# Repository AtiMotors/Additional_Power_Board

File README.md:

# Additional_Power_Board
 Additional Power board design for Vecow/Rudy integration for V3.0

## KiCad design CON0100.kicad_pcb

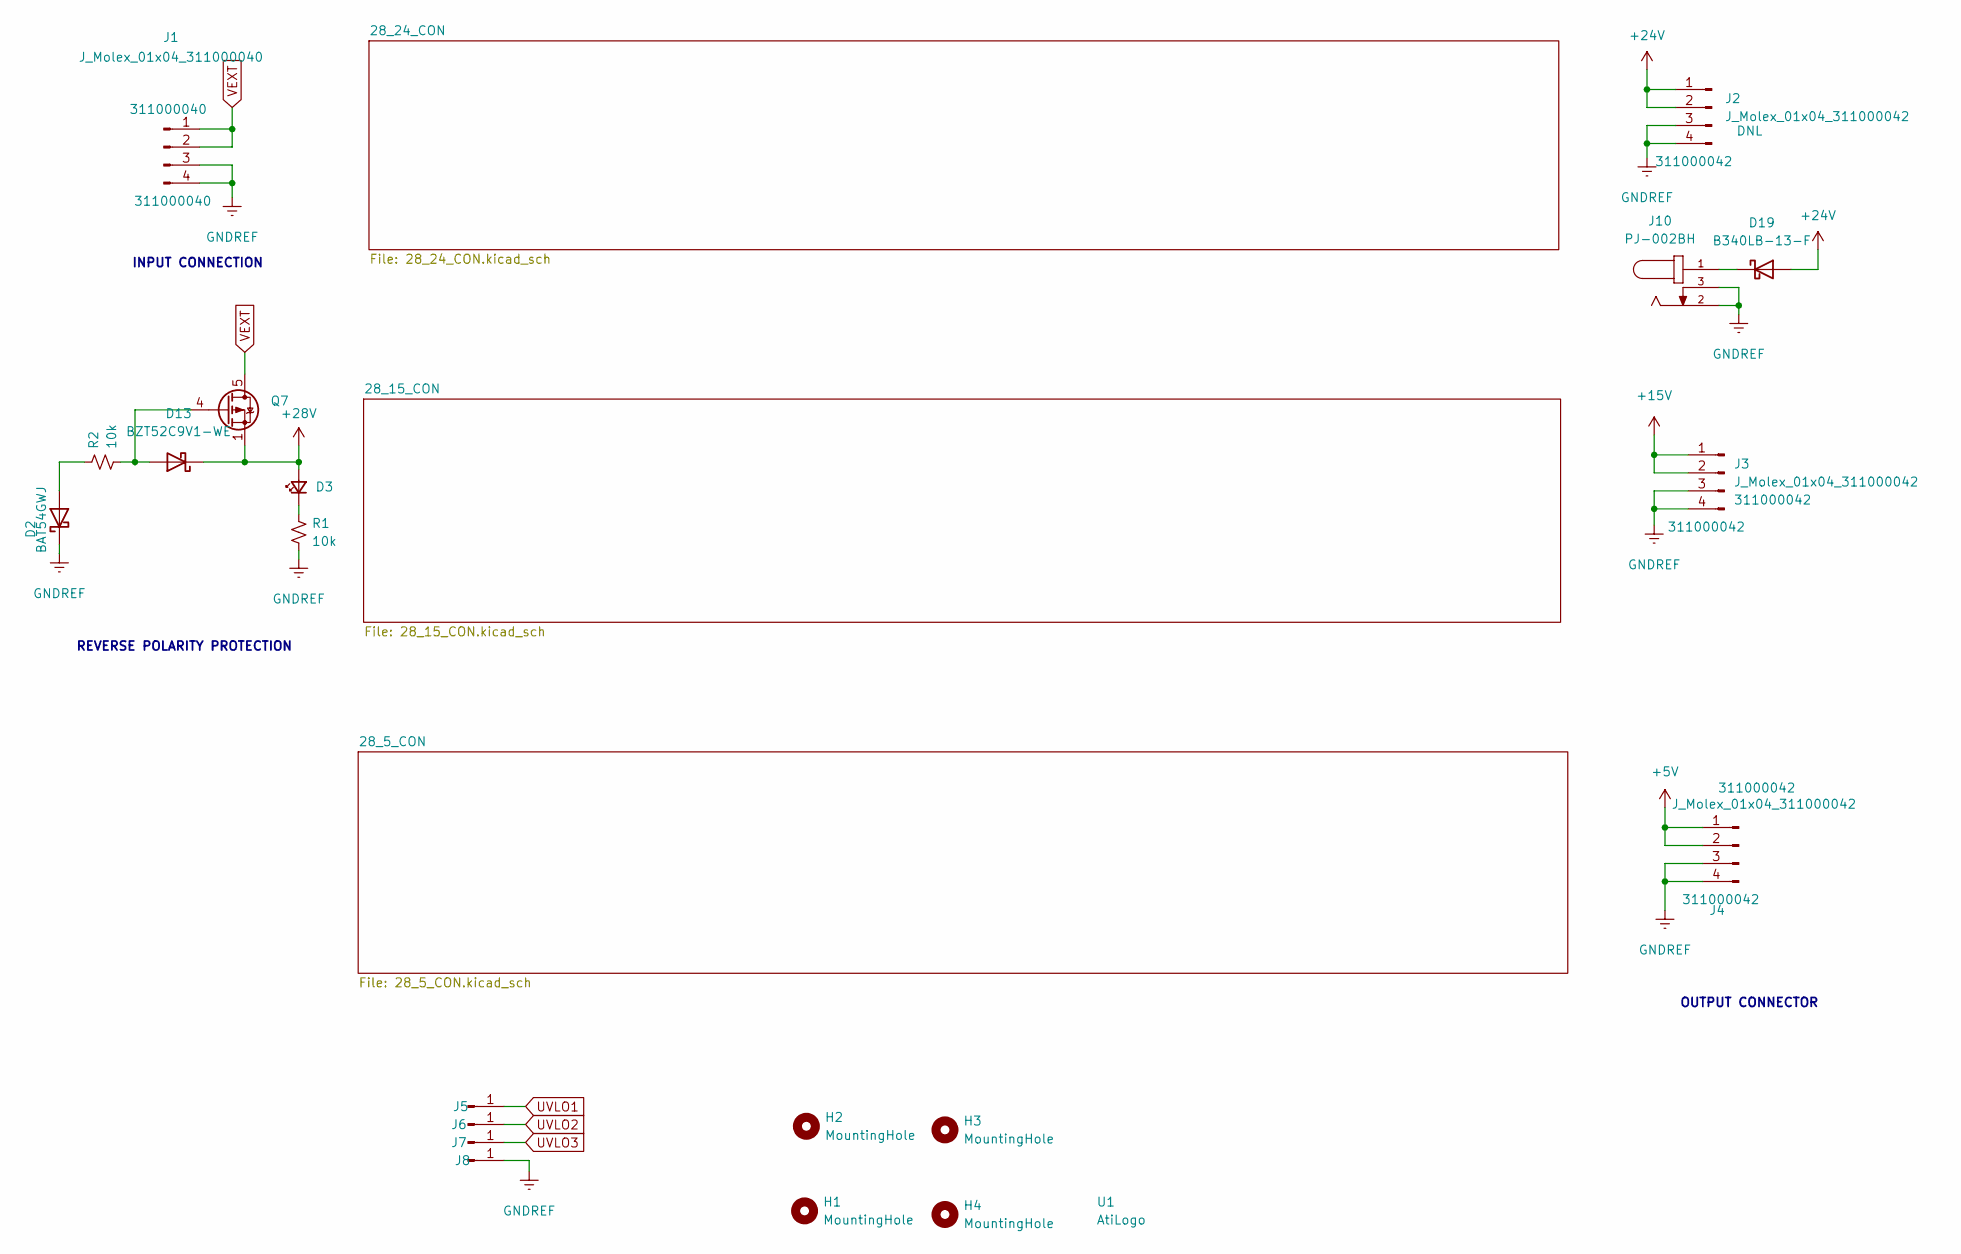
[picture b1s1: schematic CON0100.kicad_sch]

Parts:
D2: MPN BAT54GWJ
D3: D_LED_0603_Green_150060GS75000; LED_0603_1608Metric_Pad1.05x0.95mm_HandSolder; MPN 150060GS75000
D13: MPN BZT52C9V1-WE
D19: B340LB-13-F; D_SMB
H1, H2, H3, H4: MountingHole; MountingHole_3.5mm
J1: J_Molex_01x04_311000040; Molex_311000040_4pos_1row_2.54mm_PolA; MPN 311000040
J2, J3, J4: J_Molex_01x04_311000042; Molex_311000042_4pos_1row_2.54mm_PolC; MPN 311000042
J5, J6, J7, J8: Conn_01x01_Male; PinHeader_1x01_P2.54mm_Vertical
J10: PJ-002BH; CUI_PJ-002BH; MPN Manufacturer recommendations
Q7: MPN SQJ479EP-T1_GE3
R1: MPN ERJ-3EKF1002V
R2: R_10k_0603_ERJ-3EKF1002V; MPN ERJ-3EKF1002V
U1: AtiLogo; atilogo_19.06_10.16mm

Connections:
+5V: J4.1, J4.2; also elsewhere on the board
+15V: J3.1, J3.2; also elsewhere on the board
+24V: D19.2 (A), J2.1, J2.2; also elsewhere on the board
+28V: D3.2 (A), D13.1 (K), Q7.1 (S), Q7.2 (S), Q7.3 (S); also elsewhere on the board
GNDREF: D2.1 (K), J1.3, J1.4, J2.3, J2.4, J3.3, J3.4, J4.3, J4.4, J8.1, J10.2, J10.3, R1.2; also elsewhere on the board
unnamed: D2.2 (A), R2.1
unnamed: D3.1 (K), R1.1
unnamed: D19.1 (K), J10.1
unnamed: D13.2 (A), Q7.4 (G), R2.2
UVLO1: J5.1; also elsewhere on the board
UVLO2: J6.1; also elsewhere on the board
UVLO3: J7.1; also elsewhere on the board
VEXT: J1.1, J1.2, Q7.5 (D)

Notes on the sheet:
INPUT CONNECTION
REVERSE POLARITY PROTECTION
OUTPUT CONNECTOR

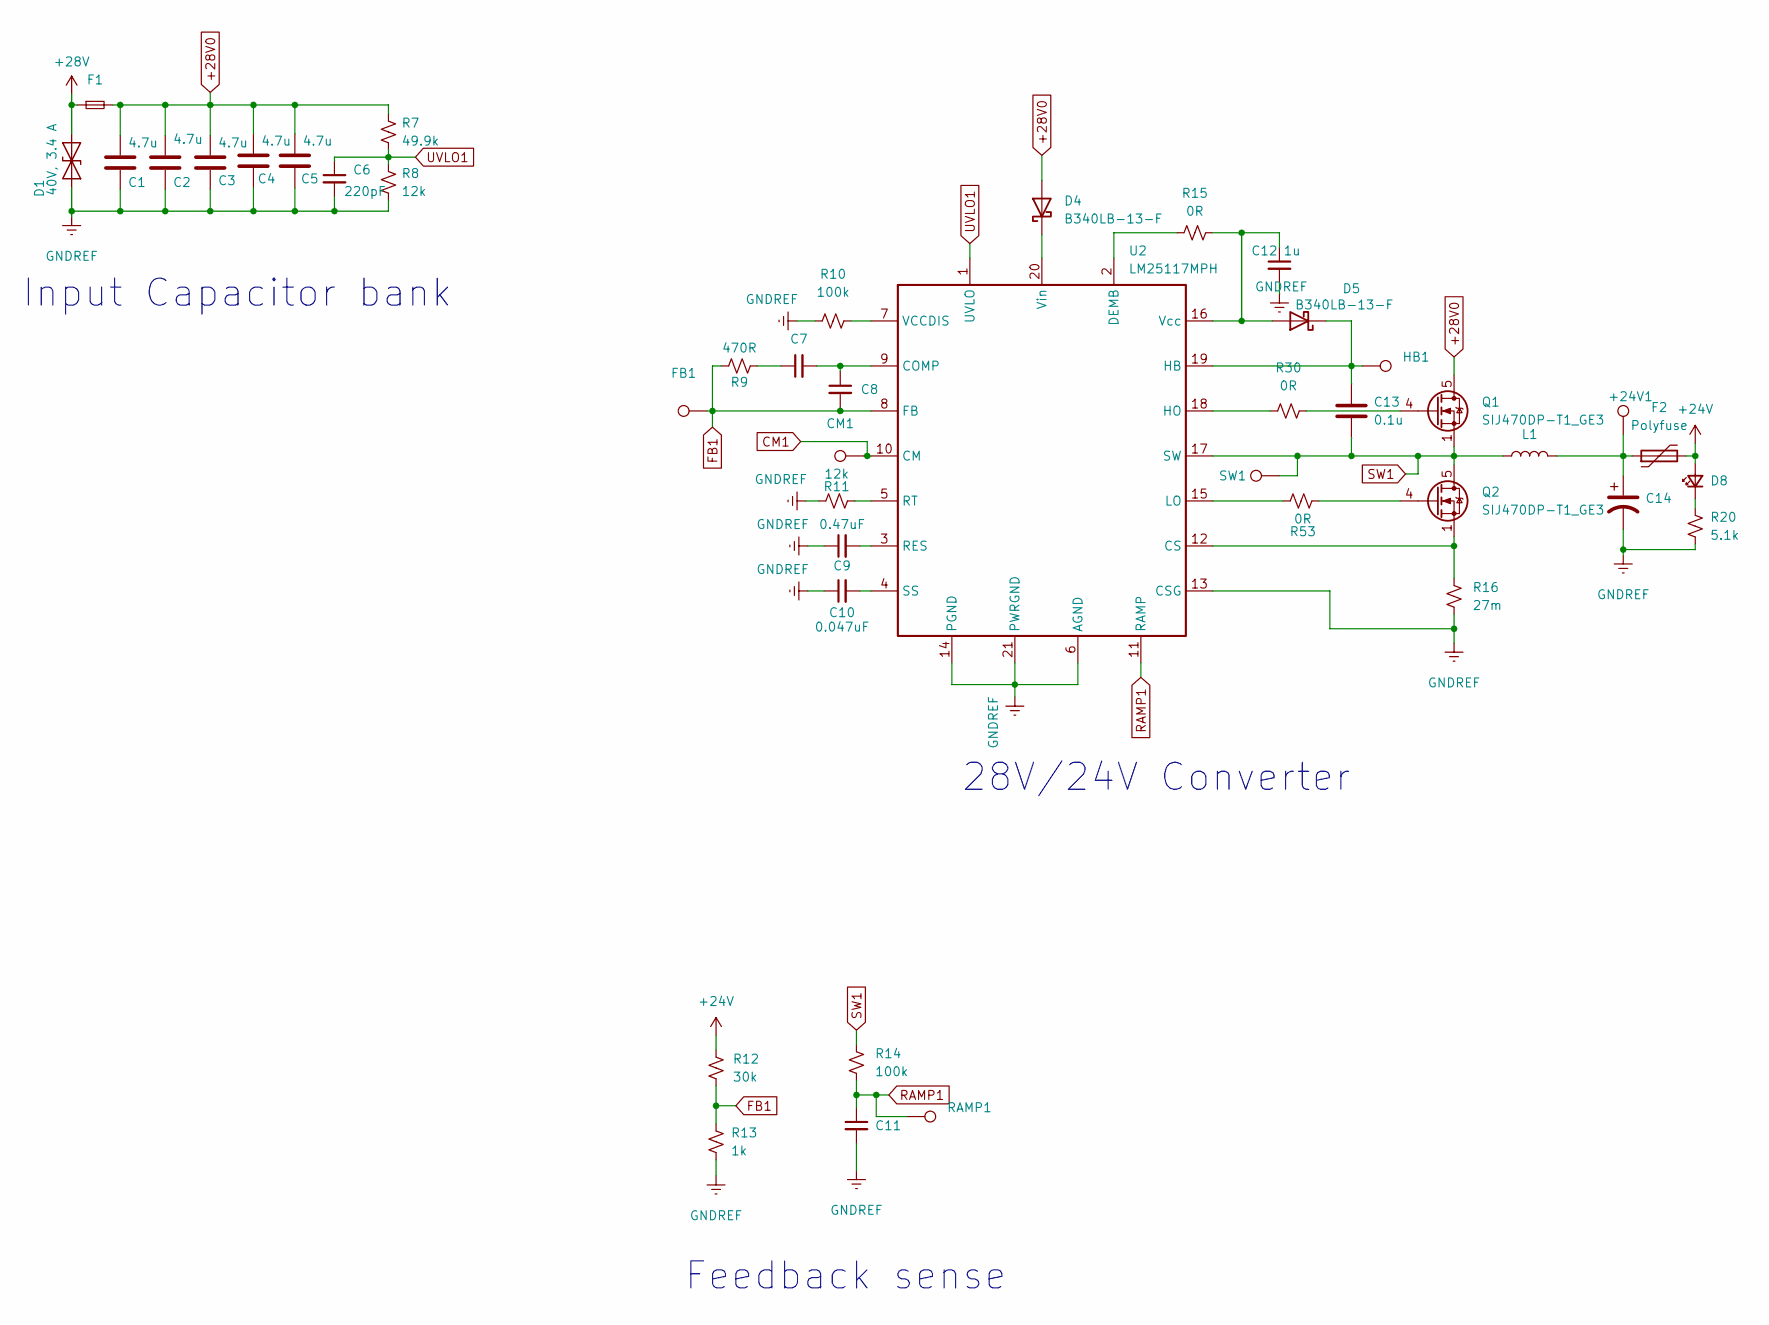
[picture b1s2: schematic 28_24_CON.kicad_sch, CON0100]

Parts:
+24V1: (no value)
C1, C2, C3, C4, C5: C_4.7u_1206_CL31B475KAHNNNE; C_1206_3216Metric_Pad1.33x1.80mm_HandSolder; MPN CL31B475KAHNNNE
C6: C_0603_220pF_50V_ECJ-1VC1H221J; C_0603_1608Metric_Pad1.08x0.95mm_HandSolder; MPN ECJ-1VC1H221J
C7: C_0.01uf_0603_50V_ECJ-1VB1H103K; C_0603_1608Metric_Pad1.08x0.95mm_HandSolder; MPN ECJ-1VB1H103K
C8: C_10pF_0603_GCM1885C1H100JA16D; C_0603_1608Metric_Pad1.08x0.95mm_HandSolder; MPN GCM1885C1H100JA16D
C9: C_0603_0.47uF_25V_CGA3E3X7R1E474K080AB; C_0603_1608Metric_Pad1.08x0.95mm_HandSolder; MPN CGA3E3X7R1E474K080AB
C10: C_0603_0.047uF_16V_10%_ECJ-1VB1C473K; C_0603_1608Metric_Pad1.08x0.95mm_HandSolder; MPN ECJ-1VB1C473K
C11: C_820pF_0603_50V_GCM1885C1H821JA16D; C_0603_1608Metric_Pad1.08x0.95mm_HandSolder; MPN GCM1885C1H821JA16D
C12: C_1uf_0603_GCJ188R71E105KA01D; C_0603_1608Metric_Pad1.08x0.95mm_HandSolder; MPN GCJ188R71E105KA01D
C13: C_0603_0.1u_50V_C0603C104K5RACAUTO; C_0603_1608Metric_Pad1.08x0.95mm_HandSolder; Voltage 50V; MPN C0603C104K5RACAUTO
C14: C_0.22uF_RAD_50V_20%; C_Elec_4x5.4; MPN UWP1HR22MCL1GB
CM1: (no value)
D1: D_TVS_40V_ATV02W360B-HF; D_SOD-123F; MPN ATV02W360B-HF
D4, D5: B340LB-13-F; D_SMB
D8: D_LED_0603_Blue_150060BS75000; LED_0603_1608Metric_Pad1.05x0.95mm_HandSolder; MPN 150060BS75000
F1: Fuse_1206_SlowBlow_SF-1206SA350M-2; Fuse_0603_1608Metric_Pad1.05x0.95mm_HandSolder; MPN SF-1206SA350M-2
F2: Polyfuse; Fuse_2920_7451Metric_Pad2.10x5.45mm_HandSolder
FB1: (no value)
HB1: (no value)
L1: L_22uH_12A_37mOhms_SMD_12.5mmx13.5mm; L_Bourns_SRP1245A; MPN SRP1265A-220M
Q1, Q2: SIJ470DP-T1_GE3; PowerPAK_SO-8_Single; MPN SIJ470DP-T1_GE3
R7: R_49.9k_0603_ERJ3EKF4992V; R_0603_1608Metric_Pad0.98x0.95mm_HandSolder; MPN ERJ-3EKF4992V
R8, R11: R_12k_0603_ERJ3EKF1202V; R_0603_1608Metric_Pad0.98x0.95mm_HandSolder; MPN ERJ-3EKF1202V
R9: R_470R_0603_ERJ-3EKF4700V; R_0603_1608Metric_Pad0.98x0.95mm_HandSolder; MPN ERJ-3EKF4700V
R10: R_100k_0603_1/10W_CRGP0603F100K; R_0603_1608Metric_Pad0.98x0.95mm_HandSolder; MPN ERJ-3EKF1003V
R12: R_30k_0603_ERJ-PB3B3002V; R_0603_1608Metric_Pad0.98x0.95mm_HandSolder; MPN ERJ-PB6B3002V
R13: R_1k_0603_ERJ-3EKF1001V; R_0603_1608Metric_Pad0.98x0.95mm_HandSolder; MPN 3EKF1001V
R14: R_100k_0603_0.1%_ERA3APB104V; R_0603_1608Metric_Pad0.98x0.95mm_HandSolder; MPN ERA3APB104V
R15, R30, R53: R_0R_0603_ERJ-3GEY0R00V; R_0603_1608Metric_Pad0.98x0.95mm_HandSolder; MPN ERJ-3GEY0R00V
R16: R_27mOhms_0805_ERJ-6BWFR027V; R_0805_2012Metric_Pad1.20x1.40mm_HandSolder; MPN ERJ-6BWFR027V
R20: R_5.1k_0603_RC0603FR-075K1L; R_0603_1608Metric_Pad0.98x0.95mm_HandSolder; MPN RC0603FR-0715KL
RAMP1: (no value)
SW1: (no value)
U2: LM25117MPH; SOP65P640X110-21N; MPN LM25117MPH/NOPB

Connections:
+24V: D8.2 (A), F2.2, R12.1; also elsewhere on the board
+28V: D1.2 (A2), F1.1; also elsewhere on the board
+28V0: C1.1, C2.1, C3.1, C4.1, C5.1, D4.2 (A), F1.2, Q1.5 (D), R7.1
CM1: CM1.1, U2.10 (CM)
FB1: C8.2, FB1.1, R9.1, R12.2, R13.1, U2.8 (FB)
GNDREF: C1.2, C2.2, C3.2, C4.2, C5.2, C6.2, C9.1, C10.1, C11.2, C12.2, C14.2, D1.1 (A1), R8.2, R10.1, R11.1, R13.2, R16.2, R20.2, U2.6 (AGND), U2.13 (CSG), U2.14 (PGND), U2.21 (PWRGND); also elsewhere on the board
unnamed: C7.1, R9.2
unnamed: C7.2, C8.1, U2.9 (COMP)
unnamed: C9.2, U2.3 (RES)
unnamed: C10.2, U2.4 (SS)
unnamed: C12.1, D5.2 (A), R15.2, U2.16 (Vcc)
unnamed: C13.1, D5.1 (K), HB1.1, U2.19 (HB)
unnamed: +24V1.1, C14.1, F2.1, L1.2
unnamed: D4.1 (K), U2.20 (Vin)
unnamed: D8.1 (K), R20.1
unnamed: Q1.4 (G), R30.2
unnamed: Q2.1 (S), Q2.2 (S), Q2.3 (S), R16.1, U2.12 (CS)
unnamed: Q2.4 (G), R53.2
unnamed: R10.2, U2.7 (VCCDIS)
unnamed: R11.2, U2.5 (RT)
unnamed: R15.1, U2.2 (DEMB)
unnamed: R30.1, U2.18 (HO)
unnamed: R53.1, U2.15 (LO)
RAMP1: C11.1, R14.2, RAMP1.1, U2.11 (RAMP)
SW1: C13.2, L1.1, Q1.1 (S), Q1.2 (S), Q1.3 (S), Q2.5 (D), R14.1, SW1.1, U2.17 (SW)
UVLO1: C6.1, R7.2, R8.1, U2.1 (UVLO); also elsewhere on the board

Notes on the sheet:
Feedback sense
28V/24V Converter
Input Capacitor bank

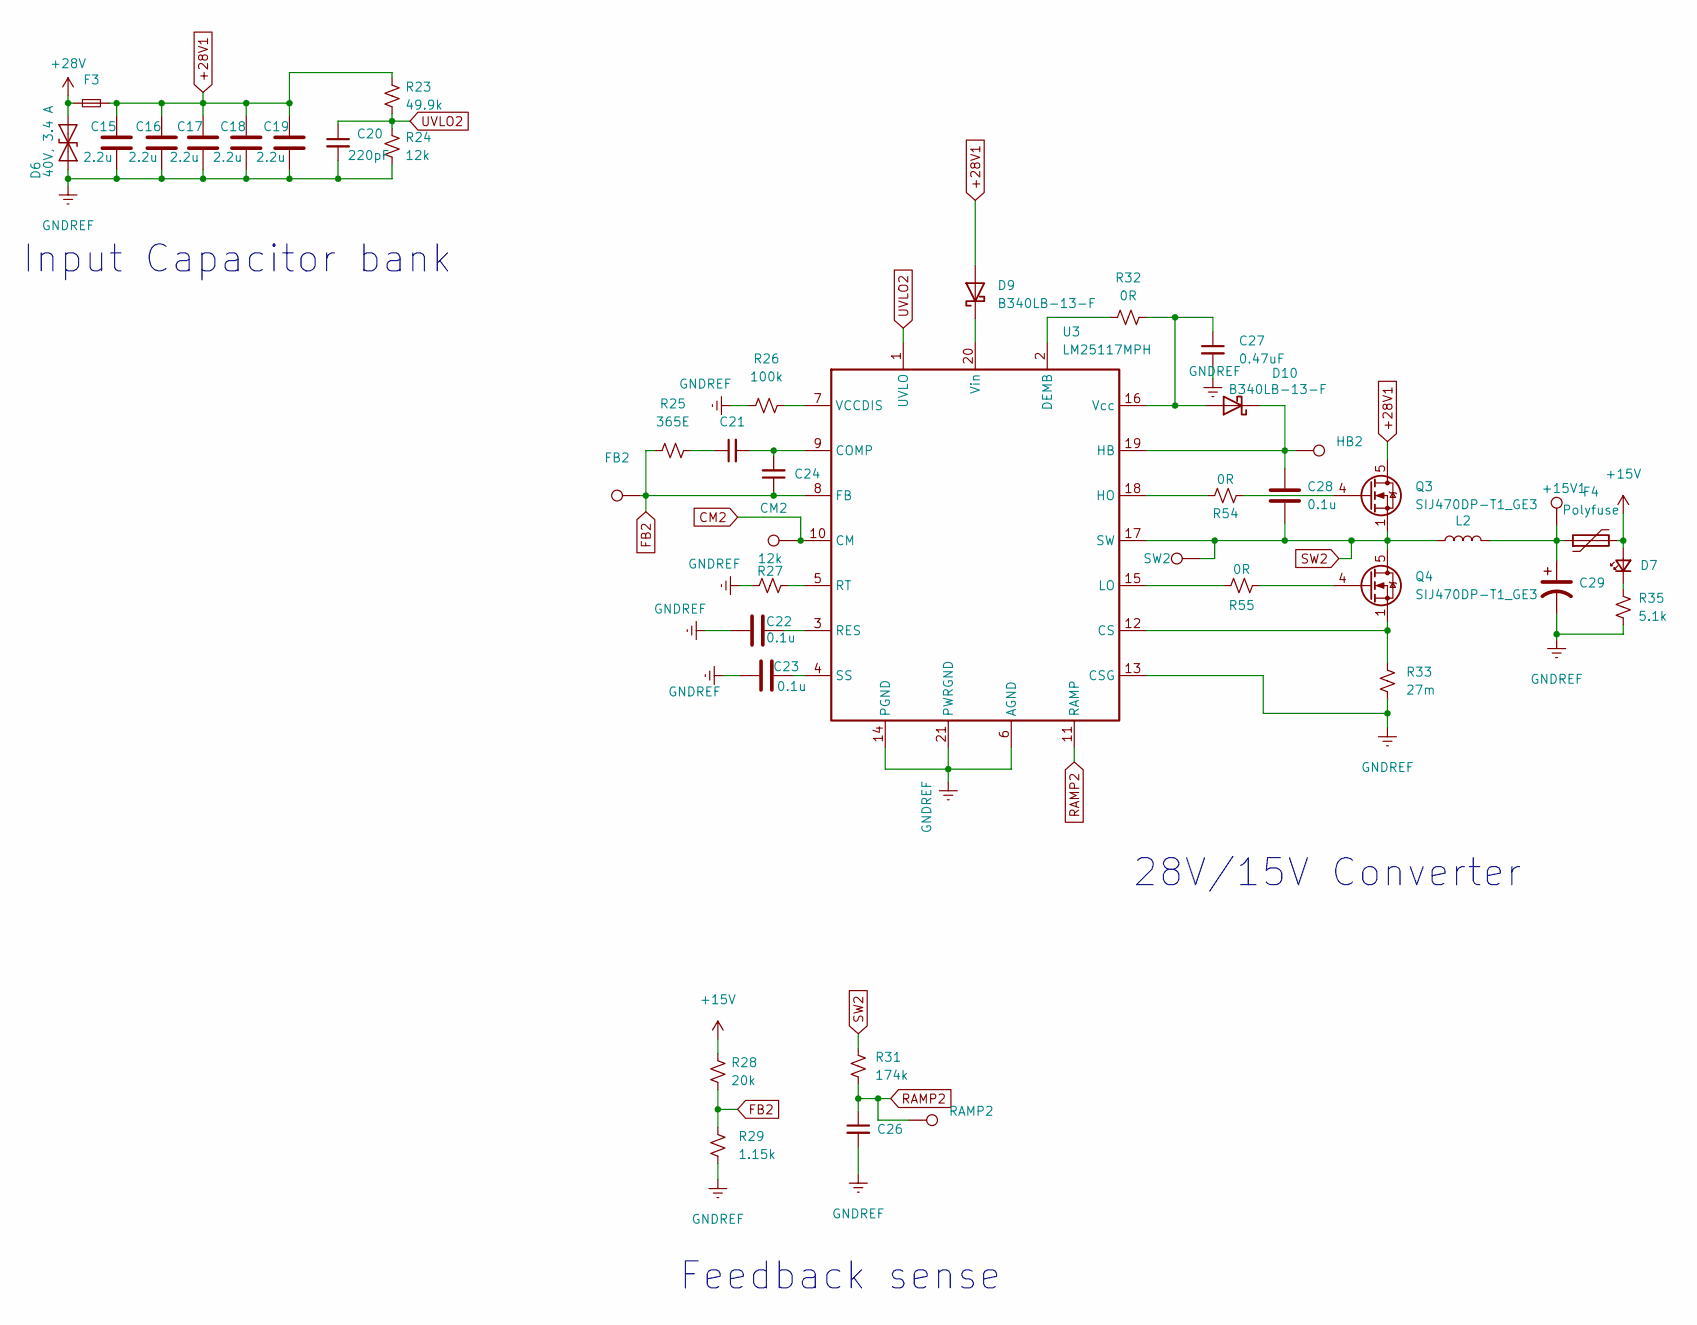
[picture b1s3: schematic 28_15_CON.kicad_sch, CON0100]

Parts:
+15V1: (no value)
C15, C16, C17, C18, C19: C_2.2u_1206_GCJ31CR71H225KA12L; C_1206_3216Metric_Pad1.33x1.80mm_HandSolder; MPN GCJ31CR71H225KA12L
C20: C_0603_220pF_50V_ECJ-1VC1H221J; C_0603_1608Metric_Pad1.08x0.95mm_HandSolder; MPN ECJ-1VC1H221J
C21: C_4700pF_0805_CL21C472JAFNNNE; C_0805_2012Metric_Pad1.18x1.45mm_HandSolder; MPN CL21C472JAFNNNE
C22, C23, C28: C_0603_0.1u_50V_C0603C104K5RACAUTO; C_0603_1608Metric_Pad1.08x0.95mm_HandSolder; Voltage 50V; MPN C0603C104K5RACAUTO
C24: C_150pF_0805_08055A151J4T4A; C_0805_2012Metric_Pad1.18x1.45mm_HandSolder; MPN 08055A151J4T4A
C26: C_820pF_0603_50V_GCM1885C1H821JA16D; C_0603_1608Metric_Pad1.08x0.95mm_HandSolder; MPN GCM1885C1H821JA16D
C27: C_0603_0.47uF_25V_CGA3E3X7R1E474K080AB; C_0603_1608Metric_Pad1.08x0.95mm_HandSolder; MPN CGA3E3X7R1E474K080AB
C29: C_0.22uF_RAD_50V_20%; C_Elec_4x5.4; MPN UWP1HR22MCL1GB
CM2: (no value)
D6: D_TVS_40V_ATV02W360B-HF; D_SOD-123F; MPN ATV02W360B-HF
D7: MPN 150060GS75000
D9, D10: B340LB-13-F; D_SMB
F3: Fuse_1206_SlowBlow_SF-1206SA350M-2; Fuse_0603_1608Metric_Pad1.05x0.95mm_HandSolder; MPN SF-1206SA350M-2
F4: Polyfuse; Fuse_2920_7451Metric_Pad2.10x5.45mm_HandSolder
FB2: (no value)
HB2: (no value)
L2: L_33uH_3A_60mOhms_SMD_12.5mmx12.5mm; L_Bourns_SRR1260; MPN SRR1260-330M
Q3, Q4: SIJ470DP-T1_GE3; PowerPAK_SO-8_Single; MPN SIJ470DP-T1_GE3
R23: R_49.9k_0603_ERJ3EKF4992V; R_0603_1608Metric_Pad0.98x0.95mm_HandSolder; MPN ERJ-3EKF4992V
R24, R27: R_12k_0603_ERJ3EKF1202V; R_0603_1608Metric_Pad0.98x0.95mm_HandSolder; MPN ERJ-3EKF1202V
R25: R_365R_0603_ERA-3AEB3650V; R_0603_1608Metric_Pad0.98x0.95mm_HandSolder; MPN 3AEB3650V
R26: R_100k_0603_1/10W_CRGP0603F100K; R_0603_1608Metric_Pad0.98x0.95mm_HandSolder; MPN ERJ-3EKF1003V
R28: R_20k_0603_ERJ-3EKF2002V; R_0603_1608Metric_Pad0.98x0.95mm_HandSolder; MPN ERJ-3EKF2002V
R29: R_1.15k_0603_ERJ-3EKF1151V; R_0603_1608Metric_Pad0.98x0.95mm_HandSolder; MPN ERJ-3EKF1151V
R31: R_174k_0603_ERJ-3EKF1743V; R_0603_1608Metric_Pad0.98x0.95mm_HandSolder; MPN ERJ-3EKF1743V
R32, R54, R55: R_0R_0603_ERJ-3GEY0R00V; R_0603_1608Metric_Pad0.98x0.95mm_HandSolder; MPN ERJ-3GEY0R00V
R33: R_27mOhms_0805_ERJ-6BWFR027V; R_0805_2012Metric_Pad1.20x1.40mm_HandSolder; MPN ERJ-6BWFR027V
R35: R_5.1k_0603_RC0603FR-075K1L; R_0603_1608Metric_Pad0.98x0.95mm_HandSolder; MPN RC0603FR-0715KL
RAMP2: (no value)
SW2: (no value)
U3: LM25117MPH; SOP65P640X110-21N; MPN LM25117MPH/NOPB

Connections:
+15V: D7.2 (A), F4.2, R28.1; also elsewhere on the board
+28V: D6.2 (A2), F3.1; also elsewhere on the board
+28V1: C15.1, C16.1, C17.1, C18.1, C19.1, D9.2 (A), F3.2, Q3.5 (D), R23.1
CM2: CM2.1, U3.10 (CM)
FB2: C24.1, FB2.1, R25.1, R28.2, R29.1, U3.8 (FB)
GNDREF: C15.2, C16.2, C17.2, C18.2, C19.2, C20.2, C22.1, C23.1, C26.2, C27.2, C29.2, D6.1 (A1), R24.2, R26.1, R27.1, R29.2, R33.2, R35.2, U3.6 (AGND), U3.13 (CSG), U3.14 (PGND), U3.21 (PWRGND); also elsewhere on the board
unnamed: C21.1, R25.2
unnamed: C21.2, C24.2, U3.9 (COMP)
unnamed: C22.2, U3.3 (RES)
unnamed: C23.2, U3.4 (SS)
unnamed: C27.1, D10.2 (A), R32.2, U3.16 (Vcc)
unnamed: C28.1, D10.1 (K), HB2.1, U3.19 (HB)
unnamed: +15V1.1, C29.1, F4.1, L2.2
unnamed: D9.1 (K), U3.20 (Vin)
unnamed: Q3.4 (G), R54.2
unnamed: Q4.1 (S), Q4.2 (S), Q4.3 (S), R33.1, U3.12 (CS)
unnamed: Q4.4 (G), R55.2
unnamed: R26.2, U3.7 (VCCDIS)
unnamed: R27.2, U3.5 (RT)
unnamed: R32.1, U3.2 (DEMB)
unnamed: D7.1 (K), R35.1
unnamed: R54.1, U3.18 (HO)
unnamed: R55.1, U3.15 (LO)
RAMP2: C26.1, R31.2, RAMP2.1, U3.11 (RAMP)
SW2: C28.2, L2.1, Q3.1 (S), Q3.2 (S), Q3.3 (S), Q4.5 (D), R31.1, SW2.1, U3.17 (SW)
UVLO2: C20.1, R23.2, R24.1, U3.1 (UVLO); also elsewhere on the board

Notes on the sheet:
28V/15V Converter
Feedback sense
Input Capacitor bank

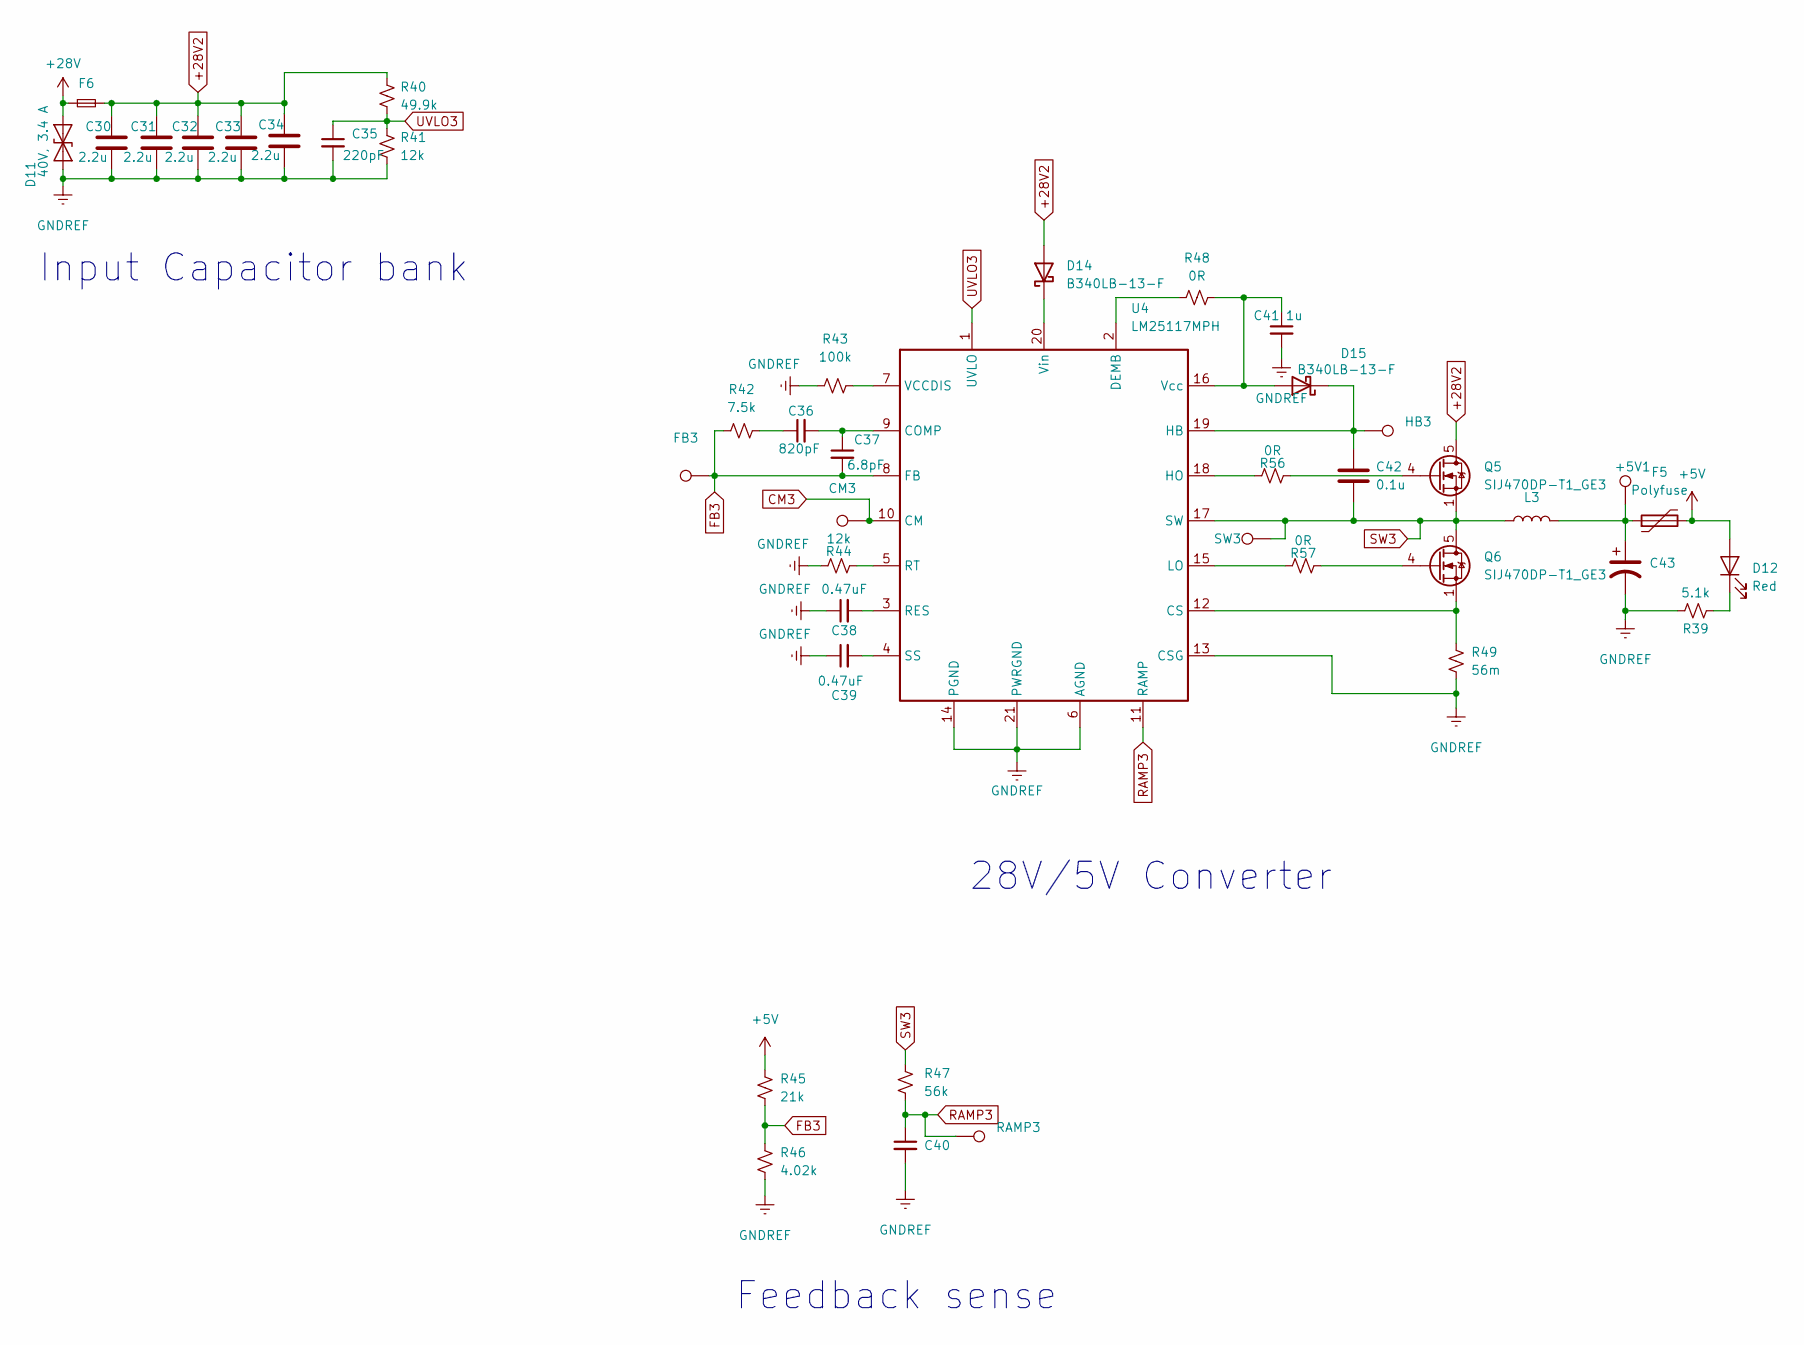
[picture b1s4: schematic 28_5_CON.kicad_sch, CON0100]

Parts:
+5V1: (no value)
C30, C31, C32, C33, C34: C_2.2u_1206_GCJ31CR71H225KA12L; C_1206_3216Metric_Pad1.33x1.80mm_HandSolder; MPN GCJ31CR71H225KA12L
C35: C_0603_220pF_50V_ECJ-1VC1H221J; C_0603_1608Metric_Pad1.08x0.95mm_HandSolder; MPN ECJ-1VC1H221J
C36, C40: C_820pF_0603_50V_GCM1885C1H821JA16D; C_0603_1608Metric_Pad1.08x0.95mm_HandSolder; MPN GCM1885C1H821JA16D
C37: C_6.8pF_0603_CL10C6R8CB8NNNC; C_0603_1608Metric_Pad1.08x0.95mm_HandSolder; MPN CL10C6R8CB8NNNC
C38, C39: C_0603_0.47uF_25V_CGA3E3X7R1E474K080AB; C_0603_1608Metric_Pad1.08x0.95mm_HandSolder; MPN CGA3E3X7R1E474K080AB
C41: C_1uf_0603_GCJ188R71E105KA01D; C_0603_1608Metric_Pad1.08x0.95mm_HandSolder; MPN GCJ188R71E105KA01D
C42: C_0603_0.1u_50V_C0603C104K5RACAUTO; C_0603_1608Metric_Pad1.08x0.95mm_HandSolder; Voltage 50V; MPN C0603C104K5RACAUTO
C43: C_3.3uF_RAD_50V_20%; C_Elec_4x5.8; MPN UUD1H3R3MCL1GS
CM3: (no value)
D11: D_TVS_40V_ATV02W360B-HF; D_SOD-123F; MPN ATV02W360B-HF
D12: MPN 150060RS75000
D14, D15: B340LB-13-F; D_SMB
F5: Polyfuse; Fuse_2920_7451Metric_Pad2.10x5.45mm_HandSolder
F6: Fuse_1206_SlowBlow_SF-1206SA350M-2; Fuse_0603_1608Metric_Pad1.05x0.95mm_HandSolder; MPN SF-1206SA350M-2
FB3: (no value)
HB3: (no value)
L3: L_27uH_5A_40mOhms_SMD_12.0mmx12.0mm; L_Bourns_SRR1210A; MPN SRR1210A-270M
Q5, Q6: SIJ470DP-T1_GE3; PowerPAK_SO-8_Single; MPN SIJ470DP-T1_GE3
R39: R_5.1k_0603_RC0603FR-075K1L; R_0603_1608Metric_Pad0.98x0.95mm_HandSolder; MPN RC0603FR-0715KL
R40: R_49.9k_0603_ERJ3EKF4992V; R_0603_1608Metric_Pad0.98x0.95mm_HandSolder; MPN ERJ-3EKF4992V
R41, R44: R_12k_0603_ERJ3EKF1202V; R_0603_1608Metric_Pad0.98x0.95mm_HandSolder; MPN ERJ-3EKF1202V
R42: R_7.5k_0603_ERA-3APB752V; R_0603_1608Metric_Pad0.98x0.95mm_HandSolder; MPN ERA-3APB752V
R43: R_100k_0603_1/10W_CRGP0603F100K; R_0603_1608Metric_Pad0.98x0.95mm_HandSolder; MPN ERJ-3EKF1003V
R45: R_21k_0603_RT0603BRD0721KL; R_0603_1608Metric_Pad0.98x0.95mm_HandSolder; MPN RT0603BRD0721KL
R46: R_4.02k_0603_RG1608P-4021-B-T5; R_0603_1608Metric_Pad0.98x0.95mm_HandSolder; MPN RG1608P-4021-B-T5
R47: R_56k_0603_ERJ-3EKF5602V; R_0603_1608Metric_Pad0.98x0.95mm_HandSolder; MPN ERJ-3EKF5602V
R48, R56, R57: R_0R_0603_ERJ-3GEY0R00V; R_0603_1608Metric_Pad0.98x0.95mm_HandSolder; MPN ERJ-3GEY0R00V
R49: R_56mOhms_0805_ERJ-6BWFR056V; R_0805_2012Metric_Pad1.20x1.40mm_HandSolder; MPN ERJ-6BWFR056V
RAMP3: (no value)
SW3: (no value)
U4: LM25117MPH; SOP65P640X110-21N; MPN LM25117MPH/NOPB

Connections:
+5V: D12.2 (A), F5.2, R45.1; also elsewhere on the board
+28V: D11.2 (A2), F6.1; also elsewhere on the board
+28V2: C30.1, C31.1, C32.1, C33.1, C34.1, D14.2 (A), F6.2, Q5.5 (D), R40.1
CM3: CM3.1, U4.10 (CM)
FB3: C37.2, FB3.1, R42.1, R45.2, R46.1, U4.8 (FB)
GNDREF: C30.2, C31.2, C32.2, C33.2, C34.2, C35.2, C38.1, C39.1, C40.2, C41.2, C43.2, D11.1 (A1), R39.1, R41.2, R43.1, R44.1, R46.2, R49.2, U4.6 (AGND), U4.13 (CSG), U4.14 (PGND), U4.21 (PWRGND); also elsewhere on the board
unnamed: C36.1, R42.2
unnamed: C36.2, C37.1, U4.9 (COMP)
unnamed: C38.2, U4.3 (RES)
unnamed: C39.2, U4.4 (SS)
unnamed: C41.1, D15.2 (A), R48.2, U4.16 (Vcc)
unnamed: C42.1, D15.1 (K), HB3.1, U4.19 (HB)
unnamed: +5V1.1, C43.1, F5.1, L3.2
unnamed: D14.1 (K), U4.20 (Vin)
unnamed: Q5.4 (G), R56.2
unnamed: Q6.1 (S), Q6.2 (S), Q6.3 (S), R49.1, U4.12 (CS)
unnamed: Q6.4 (G), R57.2
unnamed: D12.1 (K), R39.2
unnamed: R43.2, U4.7 (VCCDIS)
unnamed: R44.2, U4.5 (RT)
unnamed: R48.1, U4.2 (DEMB)
unnamed: R56.1, U4.18 (HO)
unnamed: R57.1, U4.15 (LO)
RAMP3: C40.1, R47.2, RAMP3.1, U4.11 (RAMP)
SW3: C42.2, L3.1, Q5.1 (S), Q5.2 (S), Q5.3 (S), Q6.5 (D), R47.1, SW3.1, U4.17 (SW)
UVLO3: C35.1, R40.2, R41.1, U4.1 (UVLO); also elsewhere on the board

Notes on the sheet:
Feedback sense
28V/5V Converter
Input Capacitor bank

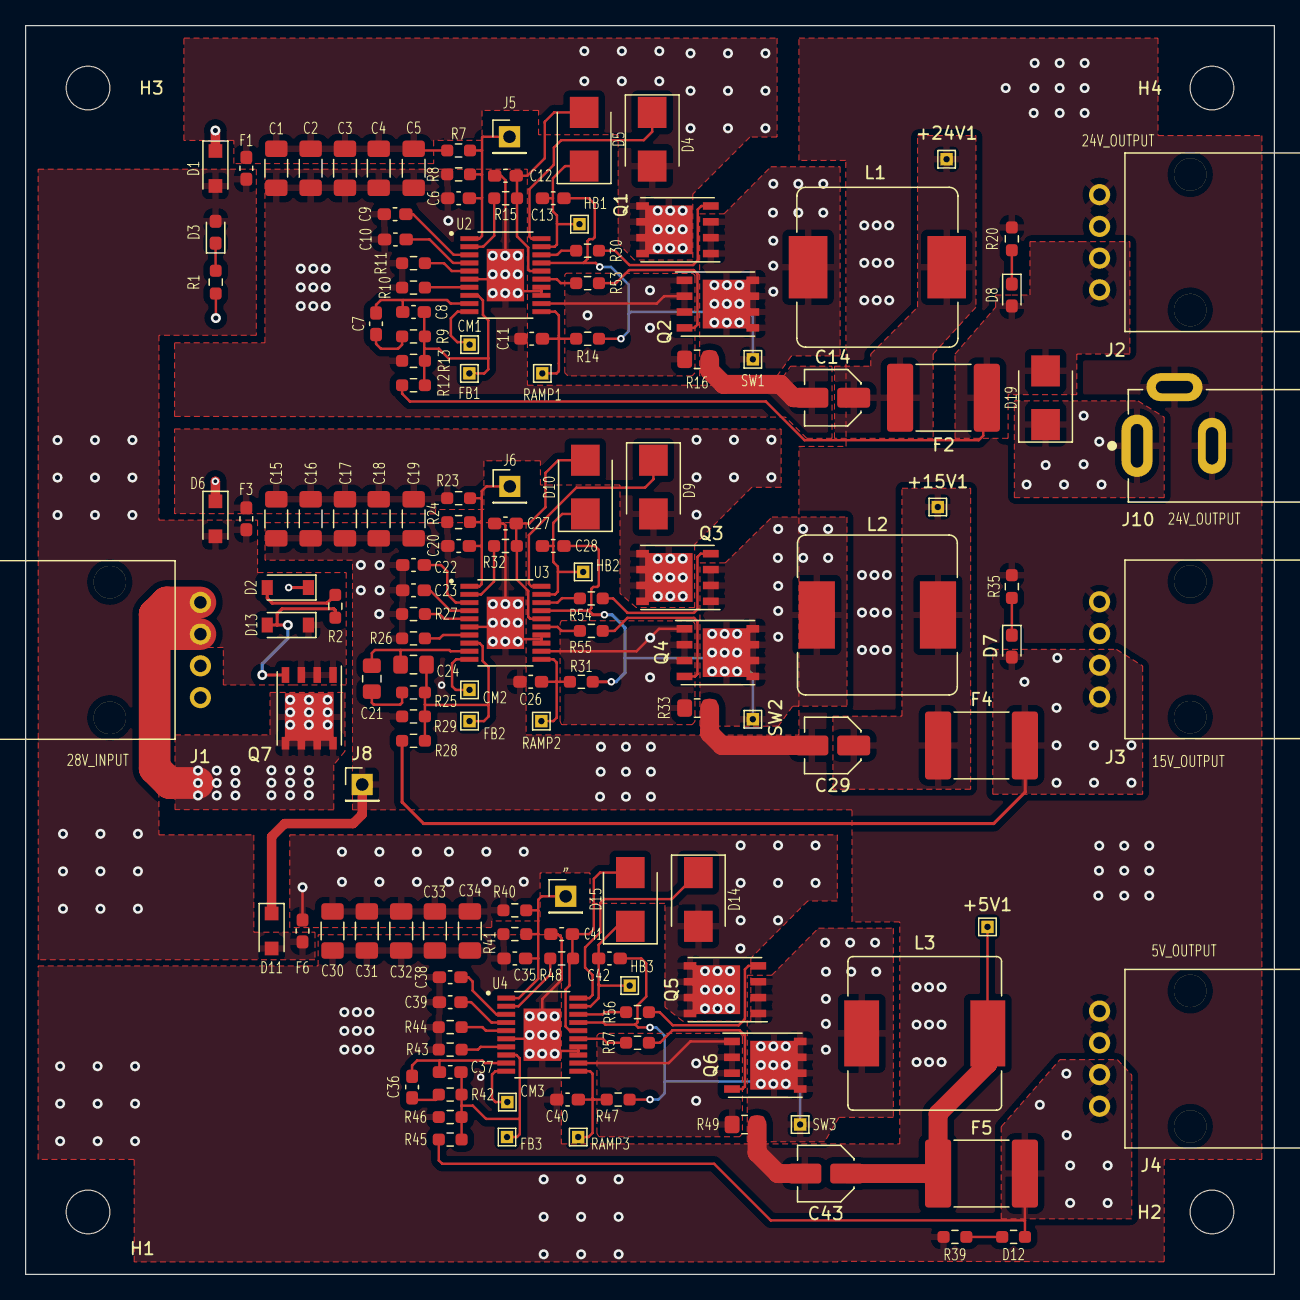
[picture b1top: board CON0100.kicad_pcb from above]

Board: 2 copper layers, 100.0 x 100.0 mm, 150 parts (1 on the bottom side), 79 nets.

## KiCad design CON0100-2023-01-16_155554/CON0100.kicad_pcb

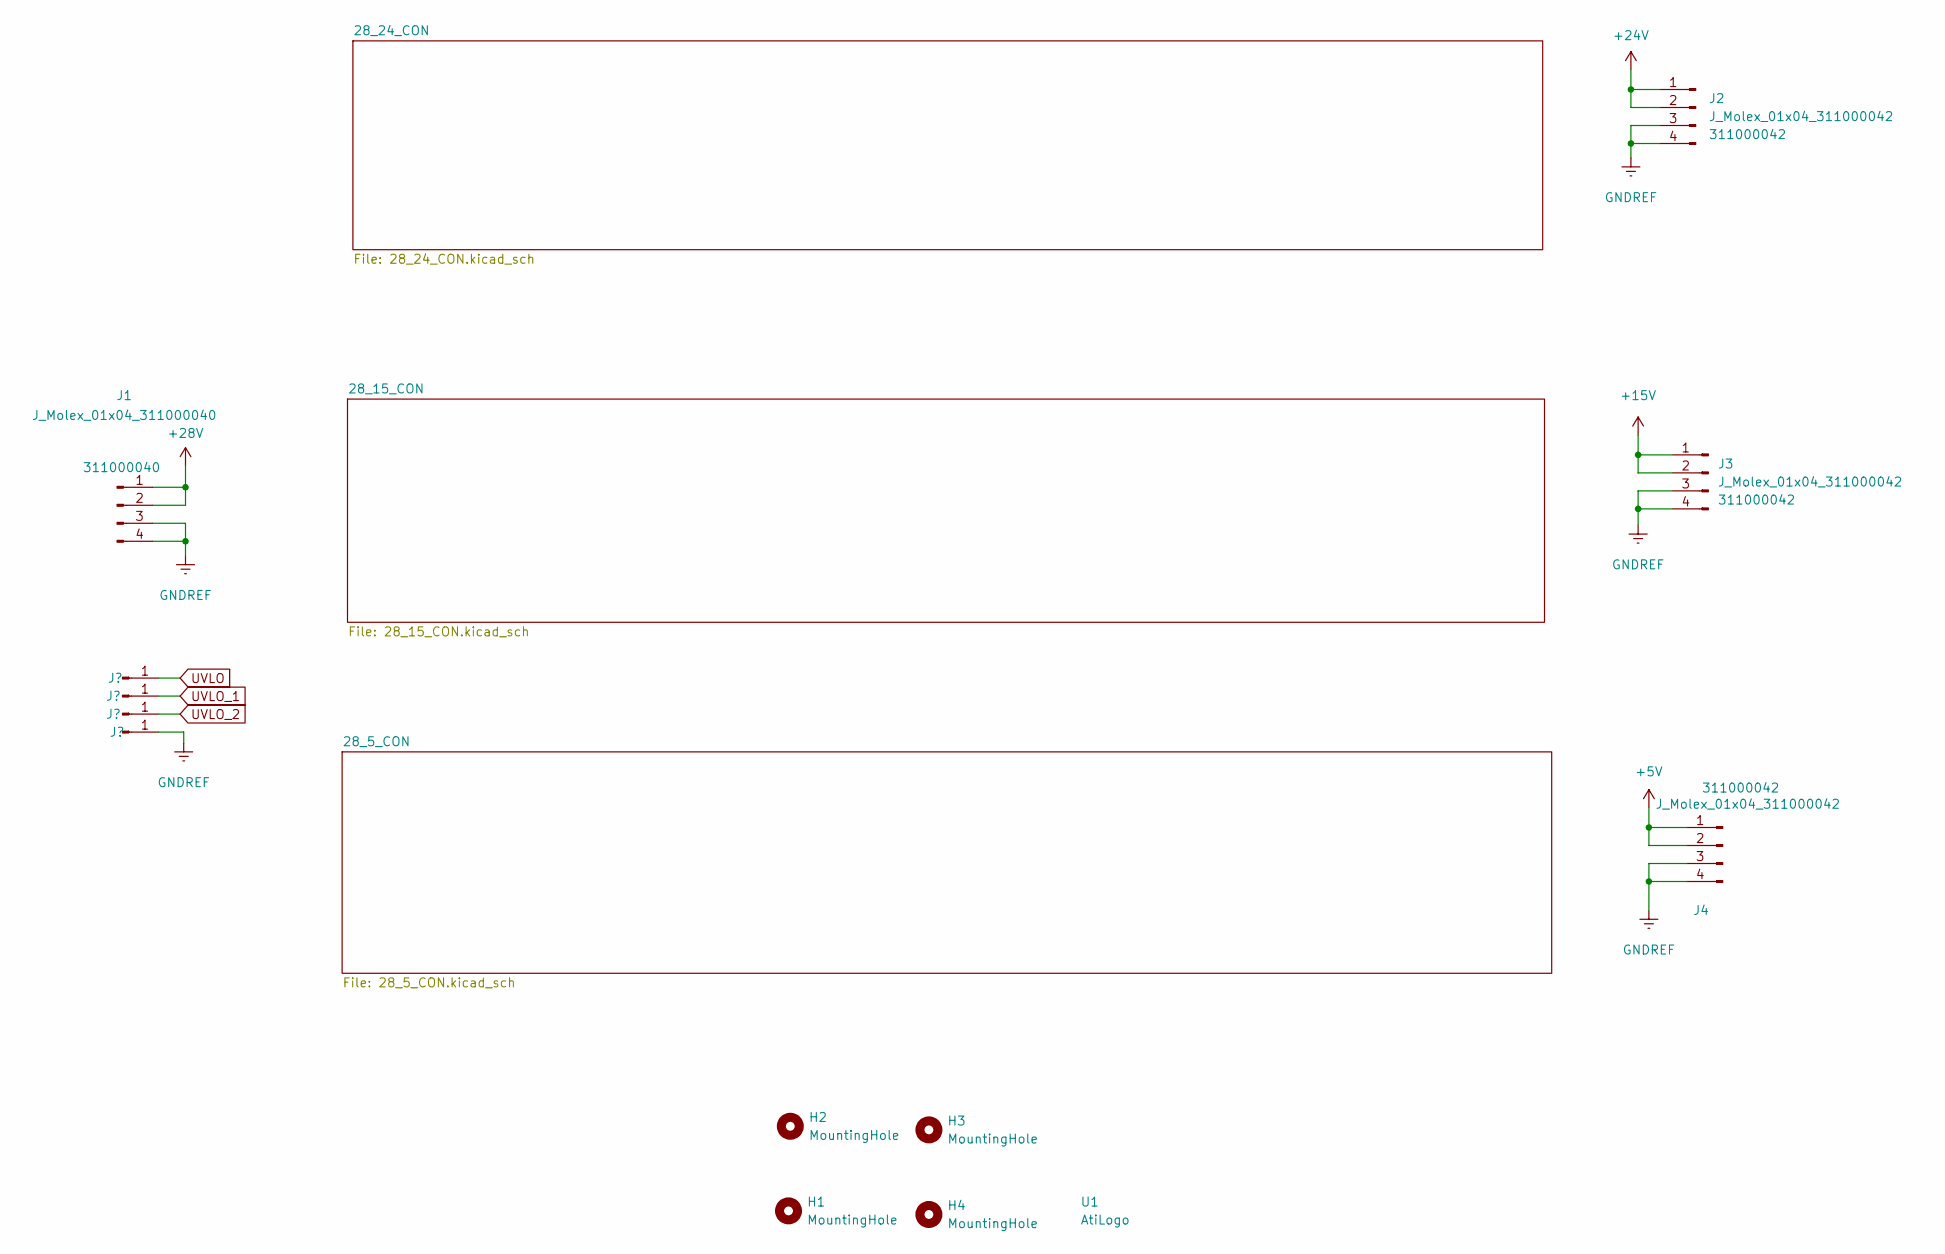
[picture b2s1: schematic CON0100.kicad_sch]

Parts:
H1, H2, H3, H4: MountingHole; MountingHole_3.5mm
J1: J_Molex_01x04_311000040; Molex_311000040_4pos_1row_2.54mm_PolA; MPN 311000040
J2, J3, J4: J_Molex_01x04_311000042; Molex_311000042_4pos_1row_2.54mm_PolC; MPN 311000042
U1: AtiLogo; atilogo_19.06_10.16mm

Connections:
+5V: J4.1, J4.2; also elsewhere on the board
+15V: J3.1, J3.2; also elsewhere on the board
+24V: J2.1, J2.2; also elsewhere on the board
+28V: J1.1, J1.2; also elsewhere on the board
GNDREF: J1.3, J1.4, J2.3, J2.4, J3.3, J3.4, J4.3, J4.4; also elsewhere on the board
